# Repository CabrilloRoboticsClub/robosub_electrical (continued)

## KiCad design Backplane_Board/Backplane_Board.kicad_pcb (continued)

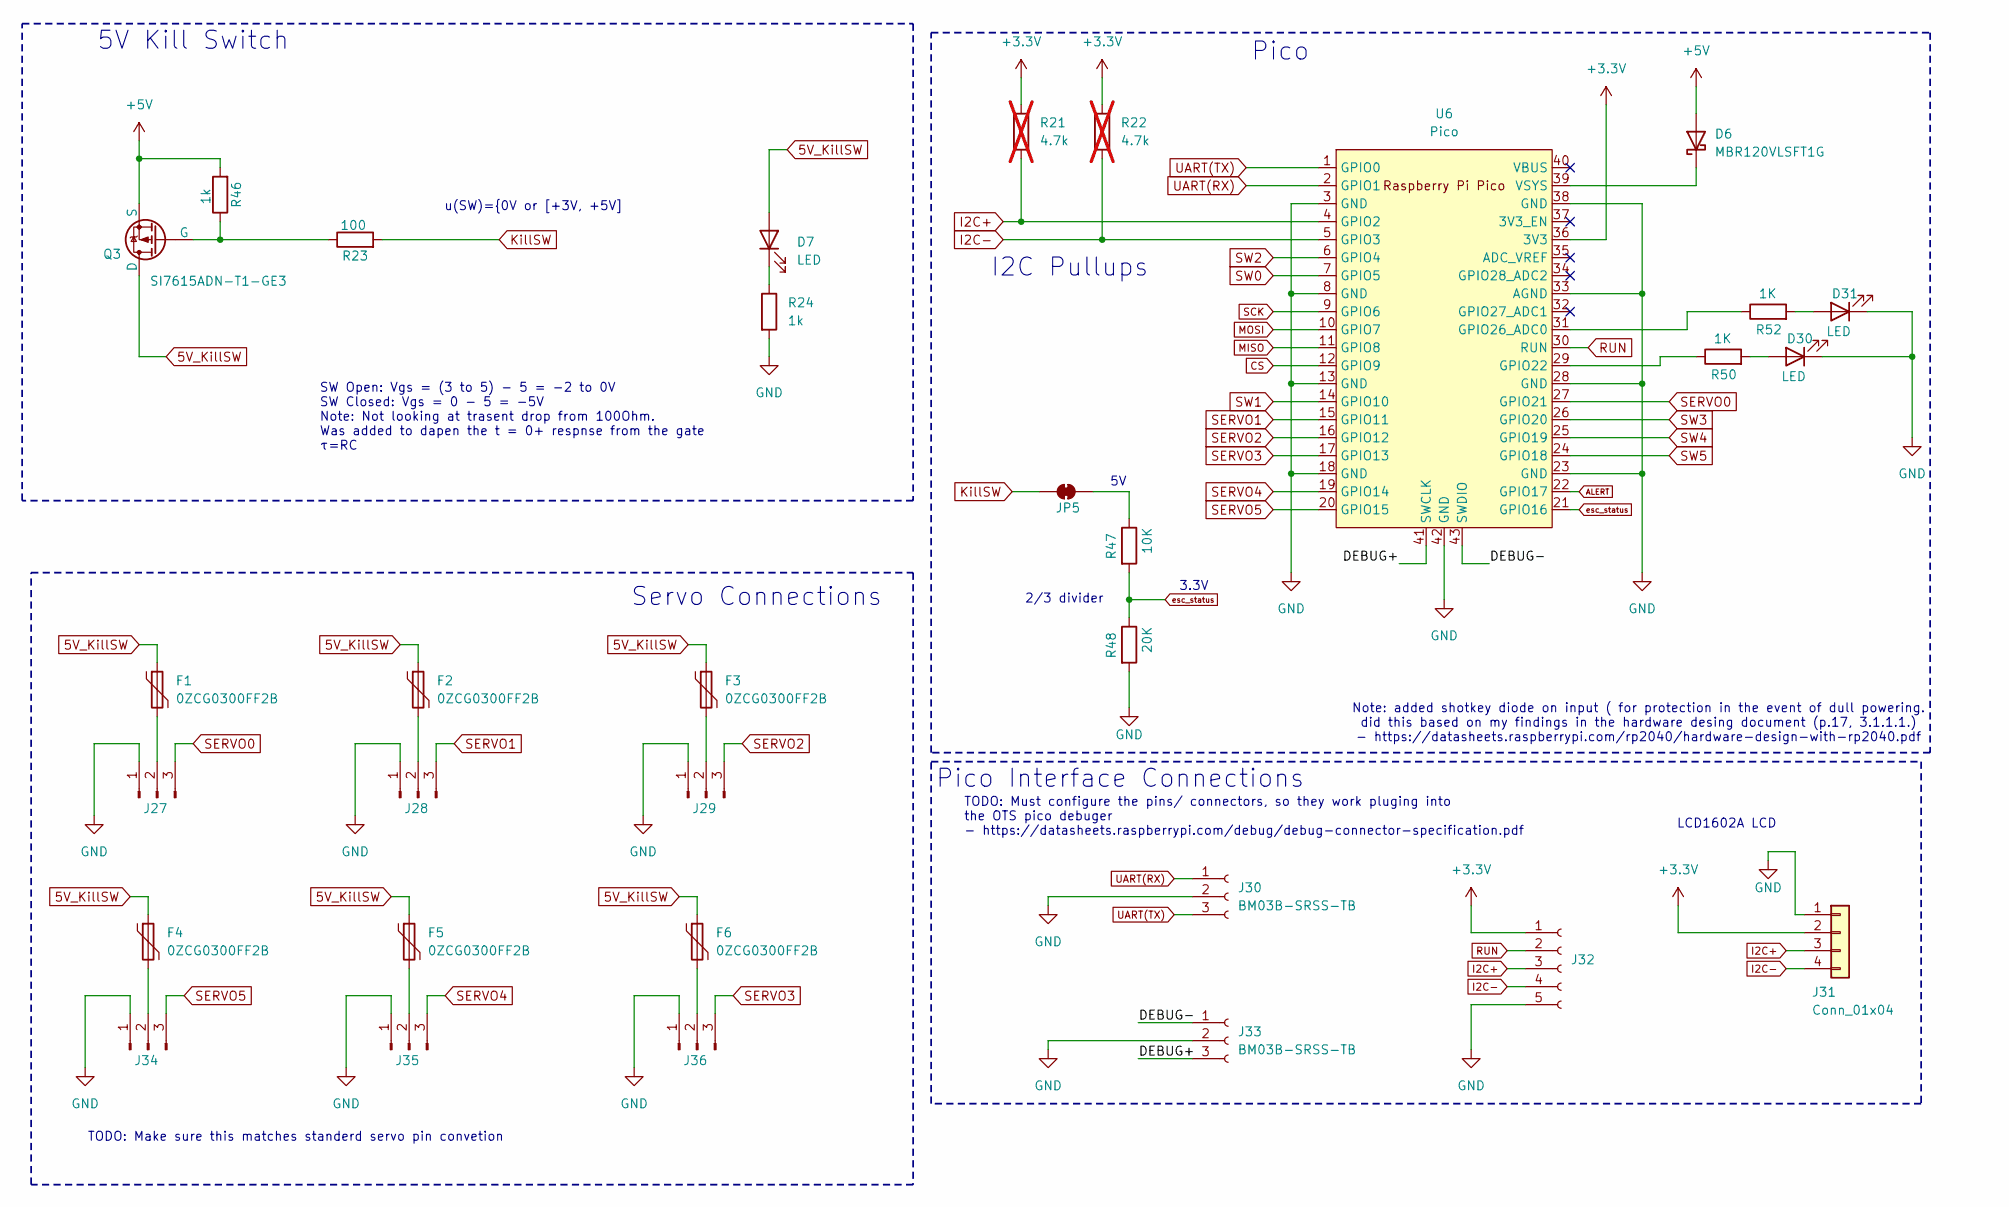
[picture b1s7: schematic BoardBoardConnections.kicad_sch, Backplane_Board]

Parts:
D6: MBR120VLSFT1G; D_SOD-123F
D7, D30, D31: LED; LED_0603_1608Metric
F1, F2, F3, F4, F5, F6: 0ZCG0300FF2B; Fuse_1812_4532Metric
J27, J28, J29, J36: Conn_01x03_Pin; PinHeader_1x03_P2.54mm_Vertical
J30, J33: BM03B-SRSS-TB; JST_SH_BM03B-SRSS-TB_1x03-1MP_P1.00mm_Vertical
J31: Conn_01x04; Molex_PicoBlade_53047-0410_1x04_P1.25mm_Vertical
J32: Conn_01x05_Socket; PinSocket_1x05_P2.54mm_Vertical
J34, J35: Connector_PinHeader_2.54mm:PinHeader_1x03_P2.54mm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; PinHeader_1x03_P2.54mm_Vertical
JP5: SolderJumper_2_Bridged; SolderJumper-2_P1.3mm_Bridged_RoundedPad1.0x1.5mm
Q3: SI7615ADN-T1-GE3; SON8_SI7615ADN-T1-GE3_VIS-L
R21, R22: 4.7k; R_1206_3216Metric_Pad1.30x1.75mm_HandSolder; not fitted
R23: 100; R_0805_2012Metric_Pad1.20x1.40mm_HandSolder
R24, R46: 1k; R_0805_2012Metric_Pad1.20x1.40mm_HandSolder
R47: 10K; R_0805_2012Metric_Pad1.20x1.40mm_HandSolder
R48: 20K; R_0805_2012Metric_Pad1.20x1.40mm_HandSolder
R50, R52: 1K; R_0805_2012Metric_Pad1.20x1.40mm_HandSolder
U6: Pico; RPi_Pico_SMD_TH

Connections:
5V_KillSW: D7.2 (A), F1.1, F2.1, F3.1, F4.1, F5.1, F6.1, Q3.1 (D); also elsewhere on the board
+3.3V: J31.2, J32.1, R21.1, R22.1, U6.36 (3V3); also elsewhere on the board
+5V: D6.2 (A), Q3.3 (S), R46.2; also elsewhere on the board
/BoardBoardConnections/DEBUG+: J33.3, U6.41 (SWCLK)
/BoardBoardConnections/DEBUG-: J33.1, U6.43 (SWDIO)
ALERT: U6.22 (GPIO17); also elsewhere on the board
CS: U6.12 (GPIO9); also elsewhere on the board
GND: D30.1 (K), D31.1 (K), J27.1, J28.1, J29.1, J30.2, J31.1, J32.5, J33.2, J34.1, J35.1, J36.1, R24.2, R48.2, U6.3 (GND), U6.8 (GND), U6.13 (GND), U6.18 (GND), U6.23 (GND), U6.28 (GND), U6.33 (AGND), U6.38 (GND), U6.42 (GND); also elsewhere on the board
I2C+: J31.3, J32.3, R21.2, U6.4 (GPIO2); also elsewhere on the board
I2C-: J31.4, J32.4, R22.2, U6.5 (GPIO3); also elsewhere on the board
KillSW: JP5.2 (B), R23.2; also elsewhere on the board
MISO: U6.11 (GPIO8); also elsewhere on the board
MOSI: U6.10 (GPIO7); also elsewhere on the board
unnamed: D6.1 (K), U6.39 (VSYS)
unnamed: D7.1 (K), R24.1
unnamed: D30.2 (A), R50.2
unnamed: D31.2 (A), R52.2
unnamed: F1.2, J27.2
unnamed: F2.2, J28.2
unnamed: F3.2, J29.2
unnamed: F4.2, J34.2
unnamed: F5.2, J35.2
unnamed: F6.2, J36.2
unnamed: JP5.1 (A), R47.1
unnamed: Q3.2 (G), R23.1, R46.1
unnamed: R50.1, U6.29 (GPIO22)
unnamed: R52.1, U6.31 (GPIO26_ADC0)
RUN: J32.2, U6.30 (RUN)
SCK: U6.9 (GPIO6); also elsewhere on the board
SERVO0: J27.3, U6.27 (GPIO21)
SERVO1: J28.3, U6.15 (GPIO11)
SERVO2: J29.3, U6.16 (GPIO12)
SERVO3: J36.3, U6.17 (GPIO13)
SERVO4: J35.3, U6.19 (GPIO14)
SERVO5: J34.3, U6.20 (GPIO15)
SW0: U6.7 (GPIO5); also elsewhere on the board
SW1: U6.14 (GPIO10); also elsewhere on the board
SW2: U6.6 (GPIO4); also elsewhere on the board
SW3: U6.26 (GPIO20); also elsewhere on the board
SW4: U6.25 (GPIO19); also elsewhere on the board
SW5: U6.24 (GPIO18); also elsewhere on the board
UART(RX): J30.1, U6.2 (GPIO1); also elsewhere on the board
UART(TX): J30.3, U6.1 (GPIO0); also elsewhere on the board
esc_status: R47.2, R48.1, U6.21 (GPIO16)

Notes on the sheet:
Pico Interface Connections
u(SW)={0V or [+3V, +5V]
Pico
SW Open: Vgs = (3 to 5) - 5 = -2 to 0V SW Closed: Vgs = 0 - 5 = -5V Note: Not looking at trasent drop from 100Ohm. Was added to dapen the t = 0+ respnse from the gate τ=RC
Note: added shotkey diode on input ( for protection in the event of dull powering. did this based on my findings in the hardware desing document (p.17, 3.1.1.1.) - https://datasheets.raspberrypi.com/rp2040/hardware-design-with-rp2040.pdf
Servo Connections
LCD1602A LCD
5V Kill Switch
TODO: Make sure this matches standerd servo pin convetion
2/3 divider
TODO: Must configure the pins/ connectors, so they work pluging into the OTS pico debuger - https://datasheets.raspberrypi.com/debug/debug-connector-specification.pdf
I2C Pullups
3.3V

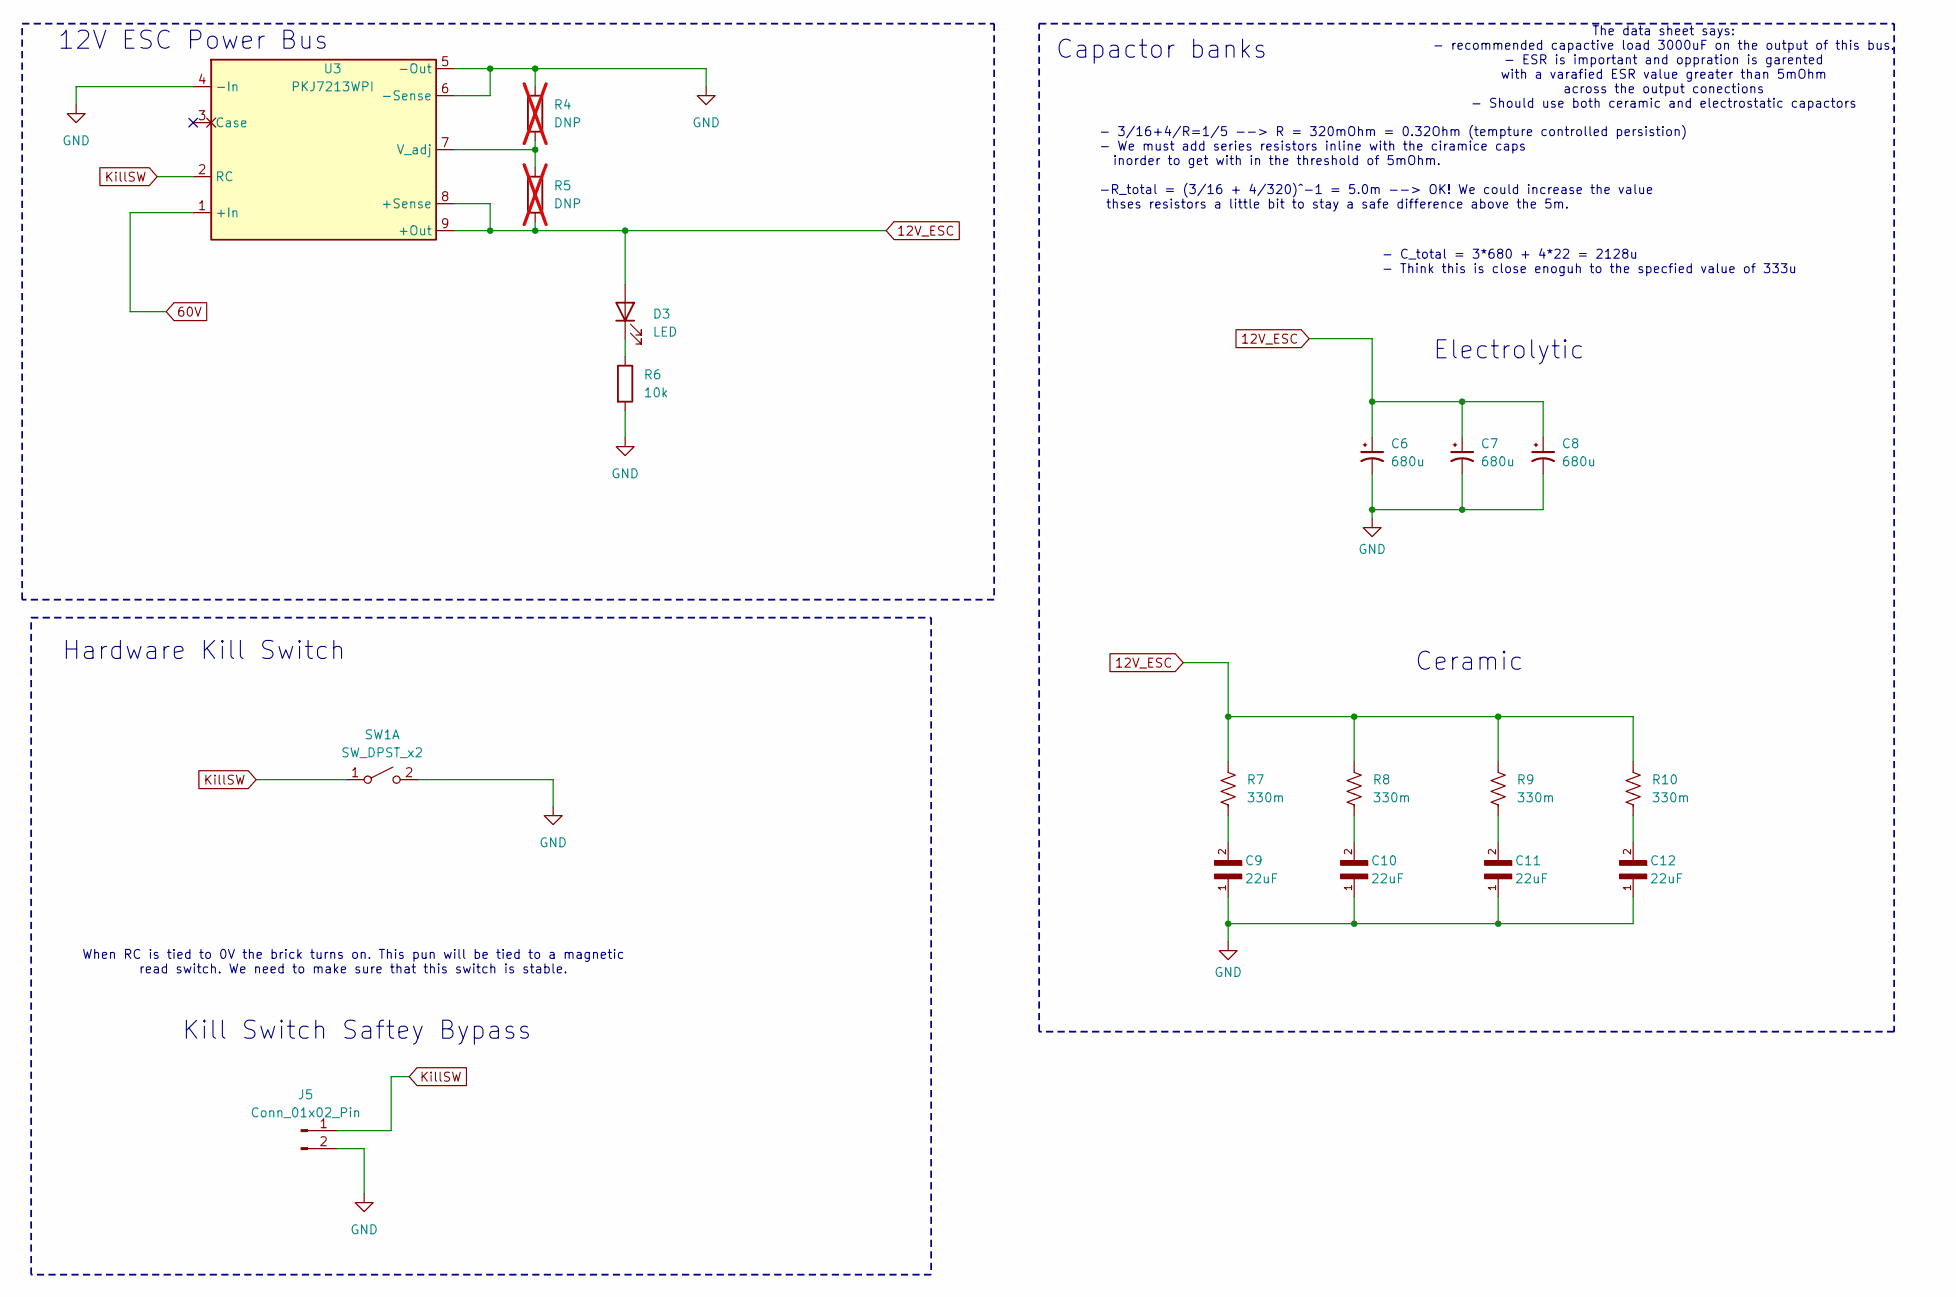
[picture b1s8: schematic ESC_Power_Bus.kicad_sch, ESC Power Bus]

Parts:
C6, C7, C8: 680u; CP_Radial_D13.0mm_P5.00mm
C9, C10, C11, C12: 22uF; C_1206_3216Metric_Pad1.33x1.80mm_HandSolder
D3: LED; LED_0603_1608Metric
J5: Conn_01x02_Pin; PinHeader_1x02_P2.54mm_Vertical
R4, R5: DNP; L_1206_3216Metric; not fitted
R6: 10k; R_0805_2012Metric_Pad1.20x1.40mm_HandSolder
R7, R8, R9, R10: 330m; RES_KDV12_OHM-L
SW1: SW_DPST_x2; TerminalBlock_Xinya_XY308-2.54-2P_1x02_P2.54mm_Horizontal
U3: PKJ7213WPI

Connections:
12V_ESC: C6.1, C7.1, C8.1, D3.2 (A), R5.2, R7.1, R8.1, R9.1, R10.1, U3.8 (+Sense), U3.9 (+Out); also elsewhere on the board
60V: U3.1 (+In); also elsewhere on the board
GND: C6.2, C7.2, C8.2, C9.1, C10.1, C11.1, C12.1, J5.2, R4.1, R6.2, SW1.2 (B), U3.4 (-In), U3.5 (-Out), U3.6 (-Sense); also elsewhere on the board
KillSW: J5.1, SW1.1 (A), U3.2 (RC); also elsewhere on the board
unnamed: C9.2, R7.2
unnamed: C10.2, R8.2
unnamed: C11.2, R9.2
unnamed: C12.2, R10.2
unnamed: D3.1 (K), R6.1
unnamed: R4.2, R5.1, U3.7 (V_adj)

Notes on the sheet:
- 3/16+4/R=1/5 --> R = 320mOhm = 0.32Ohm (tempture controlled persistion) - We must add series resistors inline with the ciramice caps inorder to get with in the threshold of 5mOhm. -R_total = (3/16 + 4/320)^-1 = 5.0m --> OK! We could increase the value thses resistors a little bit to stay a safe d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
12V ESC Power Bus
The data sheet says: - recommended capactive load 3000uF on the output of this bus. - ESR is important and oppration is garented with a varafied ESR value greater than 5mOhm across the output conections - Should use both ceramic and electrostatic capactors
Ceramic
Electrolytic
Hardware Kill Switch
- C_total = 3*680 + 4*22 = 2128u - Think this is close enoguh to the specfied value of 333u
Kill Switch Saftey Bypass
Capactor banks
When RC is tied to 0V the brick turns on. This pun will be tied to a magnetic read switch. We need to make sure that this switch is stable.

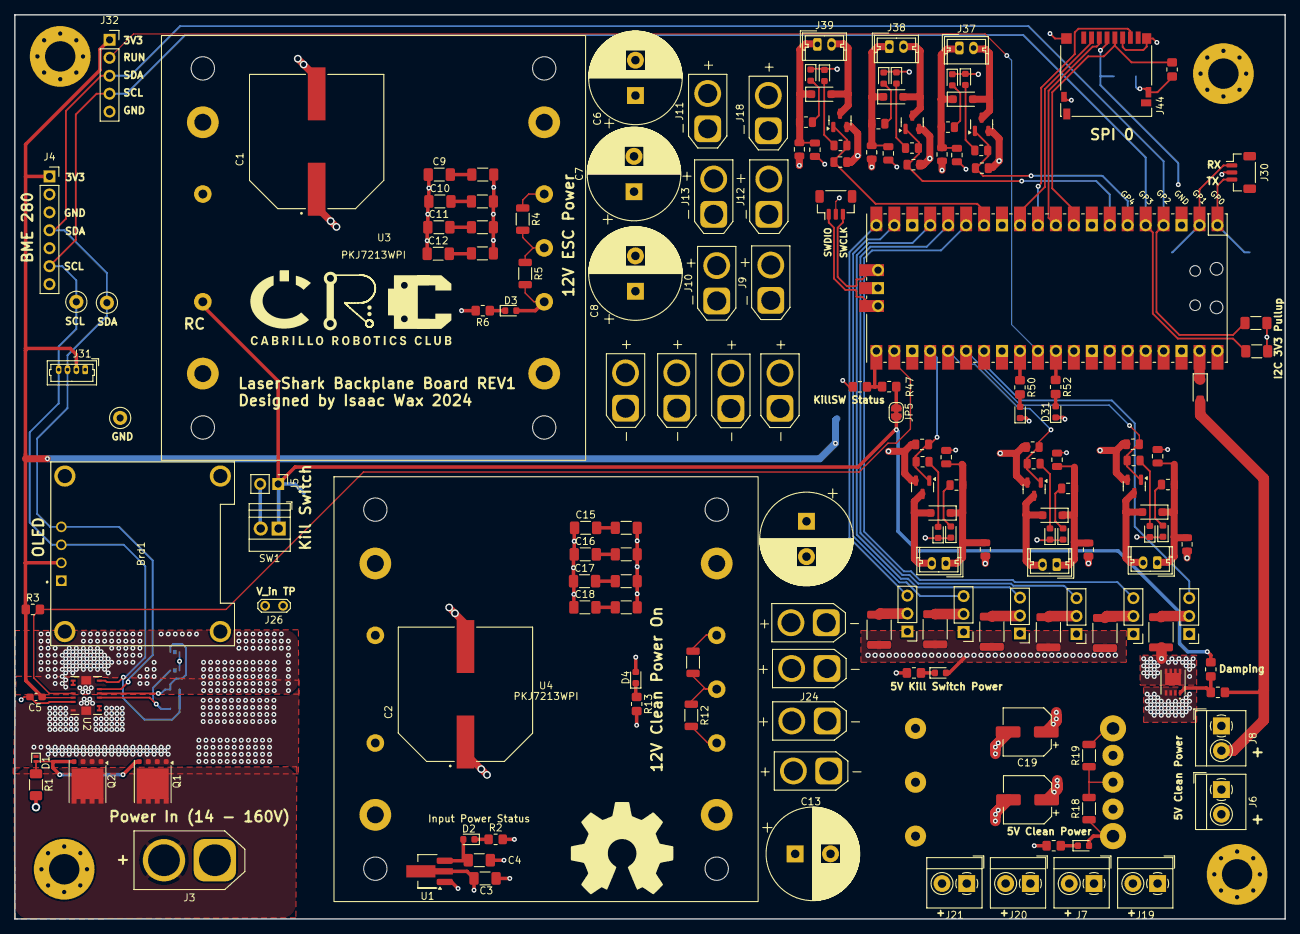
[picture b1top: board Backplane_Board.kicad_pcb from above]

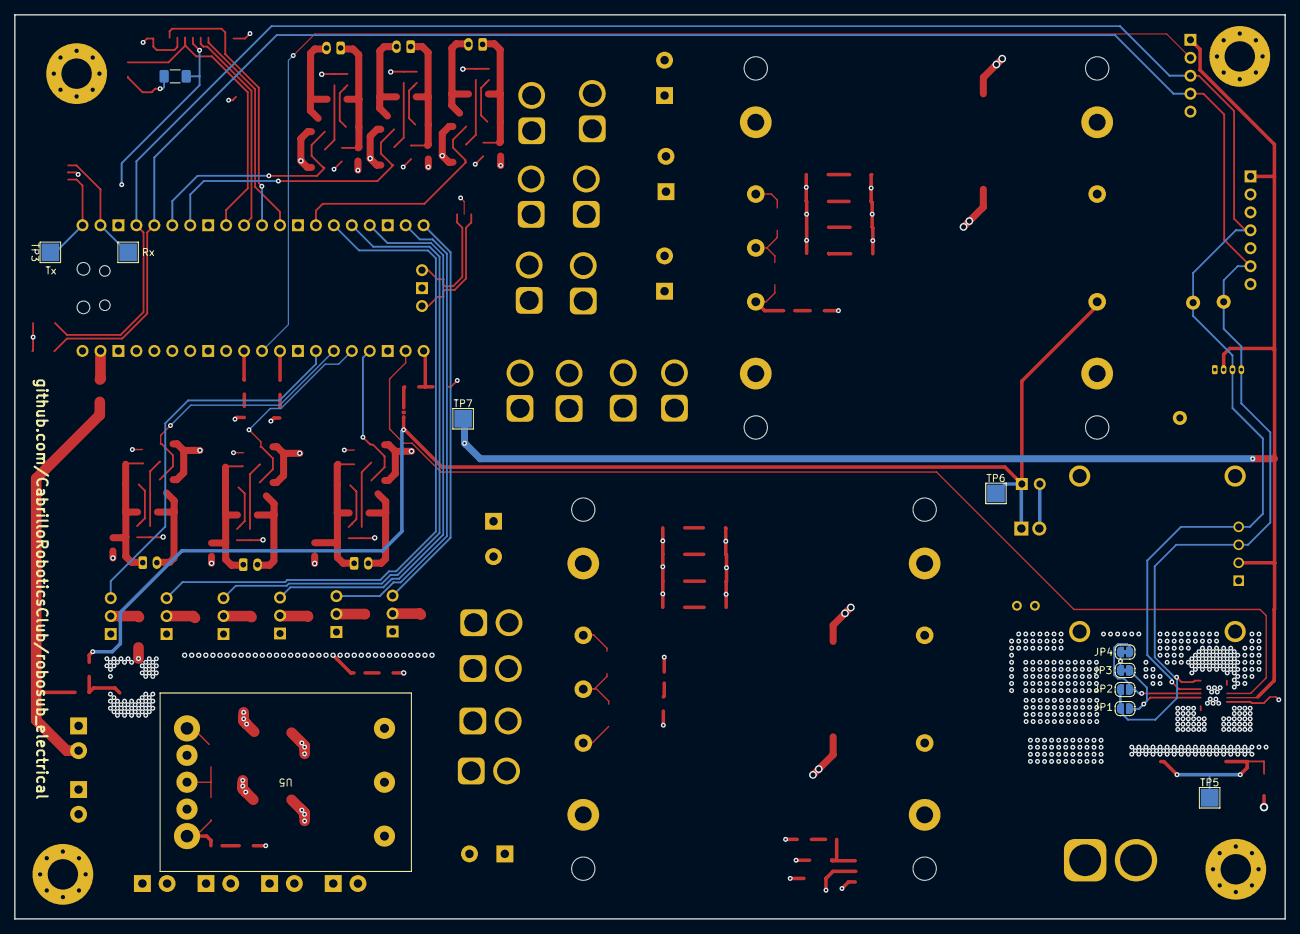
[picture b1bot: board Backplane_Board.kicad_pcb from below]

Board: 4 copper layers, 179.7 x 127.9 mm, 189 parts (11 on the bottom side), 94 nets.

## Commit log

2024-08-12 add sid
2024-08-12 Added TopLevelElectricalSID.drawio
2024-08-12 draw.io test
2024-08-14 add stackup overview
2024-08-14 more connections
2024-08-15 add sesecond sid
2024-08-16 added more detail to new page
2024-08-18 rp2040 libary test
2024-08-19 added basic rp2040 componets
2024-08-19 added esc interface pageand added test points to the rp2040 page
2024-08-21 schematic done, ready for review. need to think about how this will connect to the backplane
2024-08-23 add hardware board
2024-09-06 esc board updated
2024-09-25 added .gitattributes file so things get tracked properly
2024-09-25 added more updates
2024-09-27 added power brick symbles and added power buses to backplane board
2024-09-30 added ad converter
2024-10-02 add rerevised esc board and rough backplane schmatic
2024-10-15 backup before heavy revtion
2024-10-21 back plane board ready for review
2024-10-25 Backup current version of Backplane_Board
2024-10-25 adding dull power path ic into sepret exption board
2024-10-26 updated input revers polarity protection
2024-10-26 reviewed and cleaned up management ic
2024-10-27 spice to validate reverse polariy input protection circit
2024-10-28 more updates
2024-10-29 added series resistors on the ceramic caps to get the esr in range
2024-10-29 brick footprint
2024-10-29 from desing review 1
2024-11-01 added pico and 5v killSW
2024-11-01 added more pico stuff
2024-11-03 added power swtching circits
2024-11-05 ready for final schmatic review
2024-11-15 updated i2c pullups to 3V3 logic, not isolator needed
2024-11-19 update FET circits
2024-11-20 adding more footprints
2024-11-23 derat nest ifcation
2024-12-17 got the power input shut layout done ish
2024-12-17 layout save
2024-12-18 rough layout compleat, 200+ drc errors to fix
2024-12-18 few drc errors left - must fix fet footprints
2024-12-21 added sd card, more drc stuff to fix
2024-12-22 clean up
2024-12-23 killed more drc errors
2024-12-24 add 3d modules and clean up footprints
2025-01-21 add anotations
2025-02-01 added gerber
2025-02-02 added html bom
2025-02-17 adding pdfs for documtion reasons
